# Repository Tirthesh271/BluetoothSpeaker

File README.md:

# BluetoothSpeaker
A Bluetooth speaker implemented using an ESP32.

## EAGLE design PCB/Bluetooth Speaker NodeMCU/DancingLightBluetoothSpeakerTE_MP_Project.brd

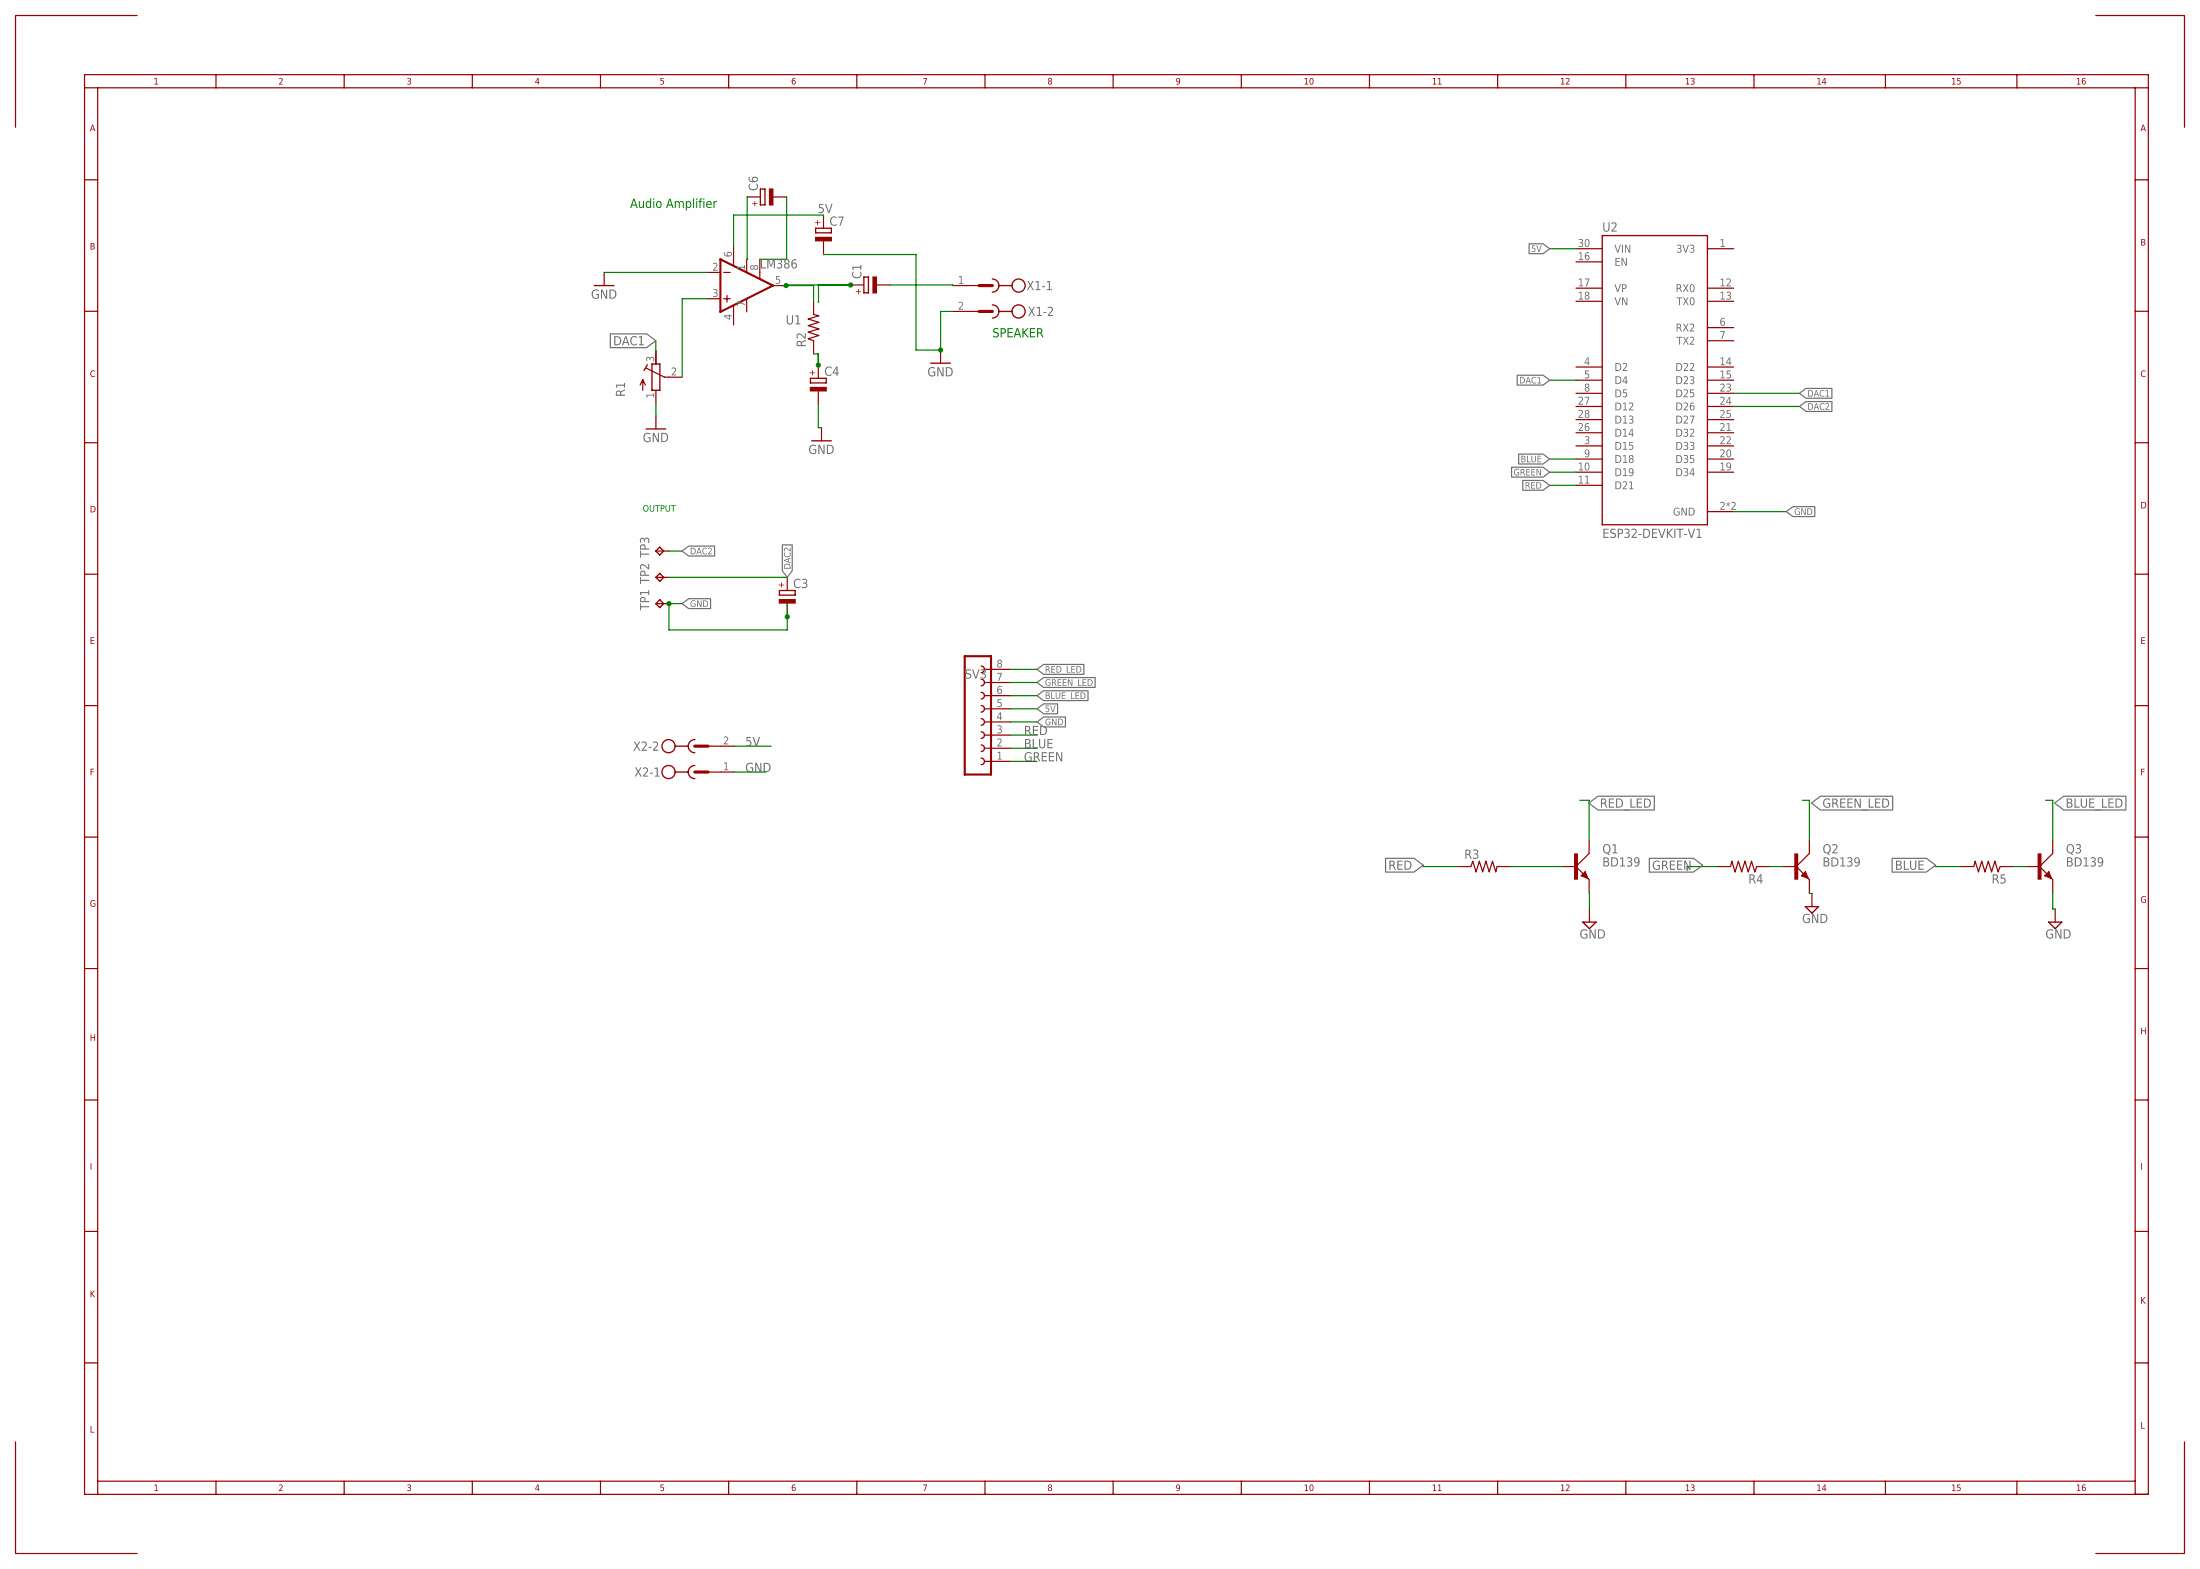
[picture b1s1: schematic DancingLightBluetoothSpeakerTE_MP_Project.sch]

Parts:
C1, C3, C4, C6, C7: CPOL-EUE2-5; E2-5
Q1, Q2, Q3: BD139; TO126AV
R1: R-TRIMM3339P; RTRIM3339P
R2, R3, R4, R5: R-US_0207/10; 0207/10
SV3: FE08-1; FE08
TP1, TP2, TP3: TPTP10SQ; TP10SQ
U1: LM386; DIP08
U2: ESP32-DEVKIT-V1; MODULE_ESP32_DEVKIT_V1
X1, X2: MSTBV2

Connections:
5V: C7.+, SV3.5, U1.6 (V+), U2.30 (VIN), X2.2
BLUE: R5.2, SV3.2, U2.9 (D18)
BLUE_LED: Q3.C, SV3.6
DAC1: R1.3 (E), U2.5 (D4), U2.23 (D25)
DAC2: C3.+, TP2.TP, TP3.TP, U2.24 (D26)
GND: C3.-, C4.-, C7.-, Q1.E, Q2.E, Q3.E, R1.1 (A), SV3.4, TP1.TP, U1.2 (-IN), U2.2 (GND), U2.29 (GND), X1.2, X2.1
GREEN: R4.2, SV3.1, U2.10 (D19)
GREEN_LED: Q2.C, SV3.7
unnamed: C1.-, X1.1
unnamed: C4.+, R2.1
unnamed: C1.+, R2.2, U1.5 (OUT)
unnamed: R1.2 (S), U1.3 (+IN)
unnamed: Q1.B, R3.2
unnamed: Q2.B, R4.1
unnamed: Q3.B, R5.1
unnamed: C6.+, U1.1 (GAIN)
unnamed: C6.-, U1.8 (GAIN)
RED: R3.1, SV3.3, U2.11 (D21)
RED_LED: Q1.C, SV3.8
V-: U1.4 (V-)

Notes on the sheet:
SPEAKER
Audio Amplifier
OUTPUT

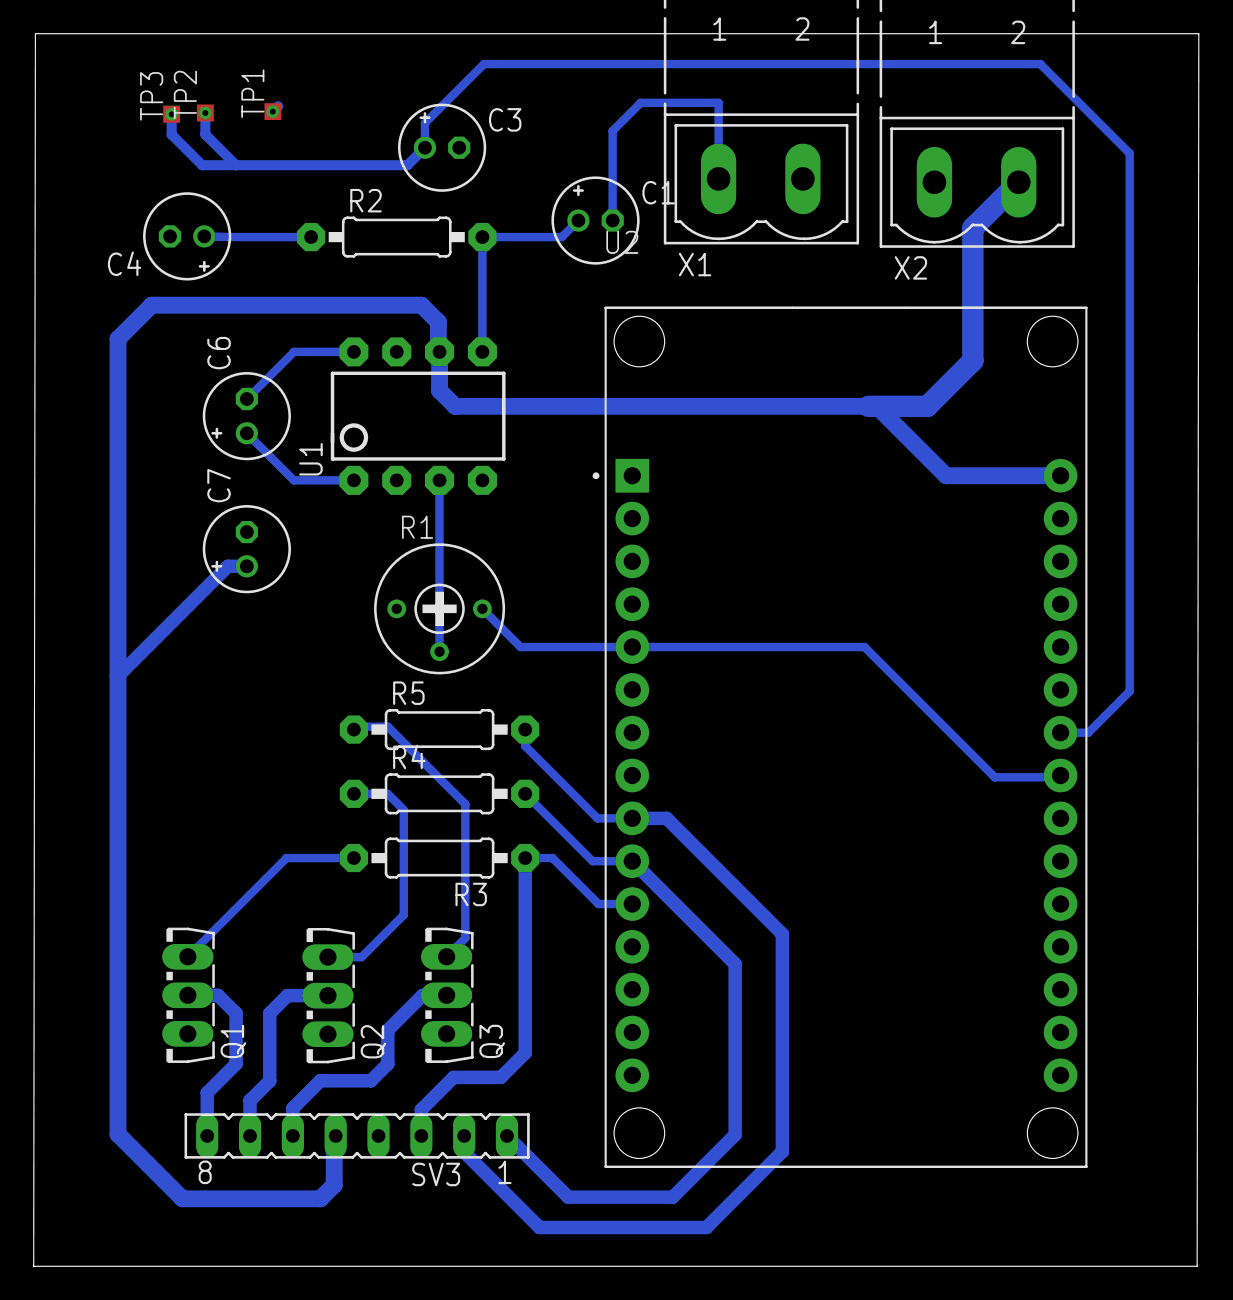
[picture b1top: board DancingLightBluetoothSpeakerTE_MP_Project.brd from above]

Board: 2 copper layers, 69.1 x 73.1 mm, 21 parts (0 on the bottom side), 19 nets.

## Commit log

2022-07-29 1st commit. Arduino Code and Eagle PCB files included.
2022-07-29 added readme
